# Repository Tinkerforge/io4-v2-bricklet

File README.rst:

IO-4 Bricklet 2.0
=================

This repository contains the firmware source code and the hardware design
files. The documentation generator configs can be found at
https://github.com/Tinkerforge/generators

Repository Content
------------------

software/:
 * examples/: Examples for all supported languages
 * build/: Compiled files
 * src/: Source code of firmware
 * Makefile: Makefile to build project

hardware/:
 * Contains KiCad project files and additionally schematics as PDF

datasheets/:
 * Contains datasheets for sensors and complex ICs that are used

Hardware
--------

The hardware is designed with the open source EDA Suite KiCad
(http://www.kicad.org). Before you are able to open the files,
you have to install the Tinkerforge kicad-libraries
(https://github.com/Tinkerforge/kicad-libraries). You can either clone
them directly in hardware/ or clone them in a separate folder and
symlink them into hardware/
(ln -s kicad_path/kicad-libraries project_path/hardware). After that you
can open the .pro file in hardware/ with KiCad and from there view and
modify the schematics and the PCB layout.

Software
--------

If you want to do your own Brick/Bricklet firmware development we highly
recommend that you use our build environment setup script and read the
tutorial (https://www.tinkerforge.com/en/doc/Tutorials/Tutorial_Build_Environment/Tutorial.html).

To compile the C code we recommend you to install the newest GNU Arm Embedded
Toolchain (https://launchpad.net/gcc-arm-embedded/+download).
You also need to install bricklib2 (https://github.com/Tinkerforge/bricklib2).

You can either clone it directly in software/src/ or clone it in a
separate folder and symlink it into software/src/
(ln -s bricklib_path/bricklib2 project_path/software/src/). Finally make sure to
have CMake installed (http://www.cmake.org/cmake/resources/software.html).

After that you can build the firmware by invoking make in software/.
The firmware (.zbin) can then be found in software/build/ and uploaded
with brickv (click button "Flashing" on start screen).

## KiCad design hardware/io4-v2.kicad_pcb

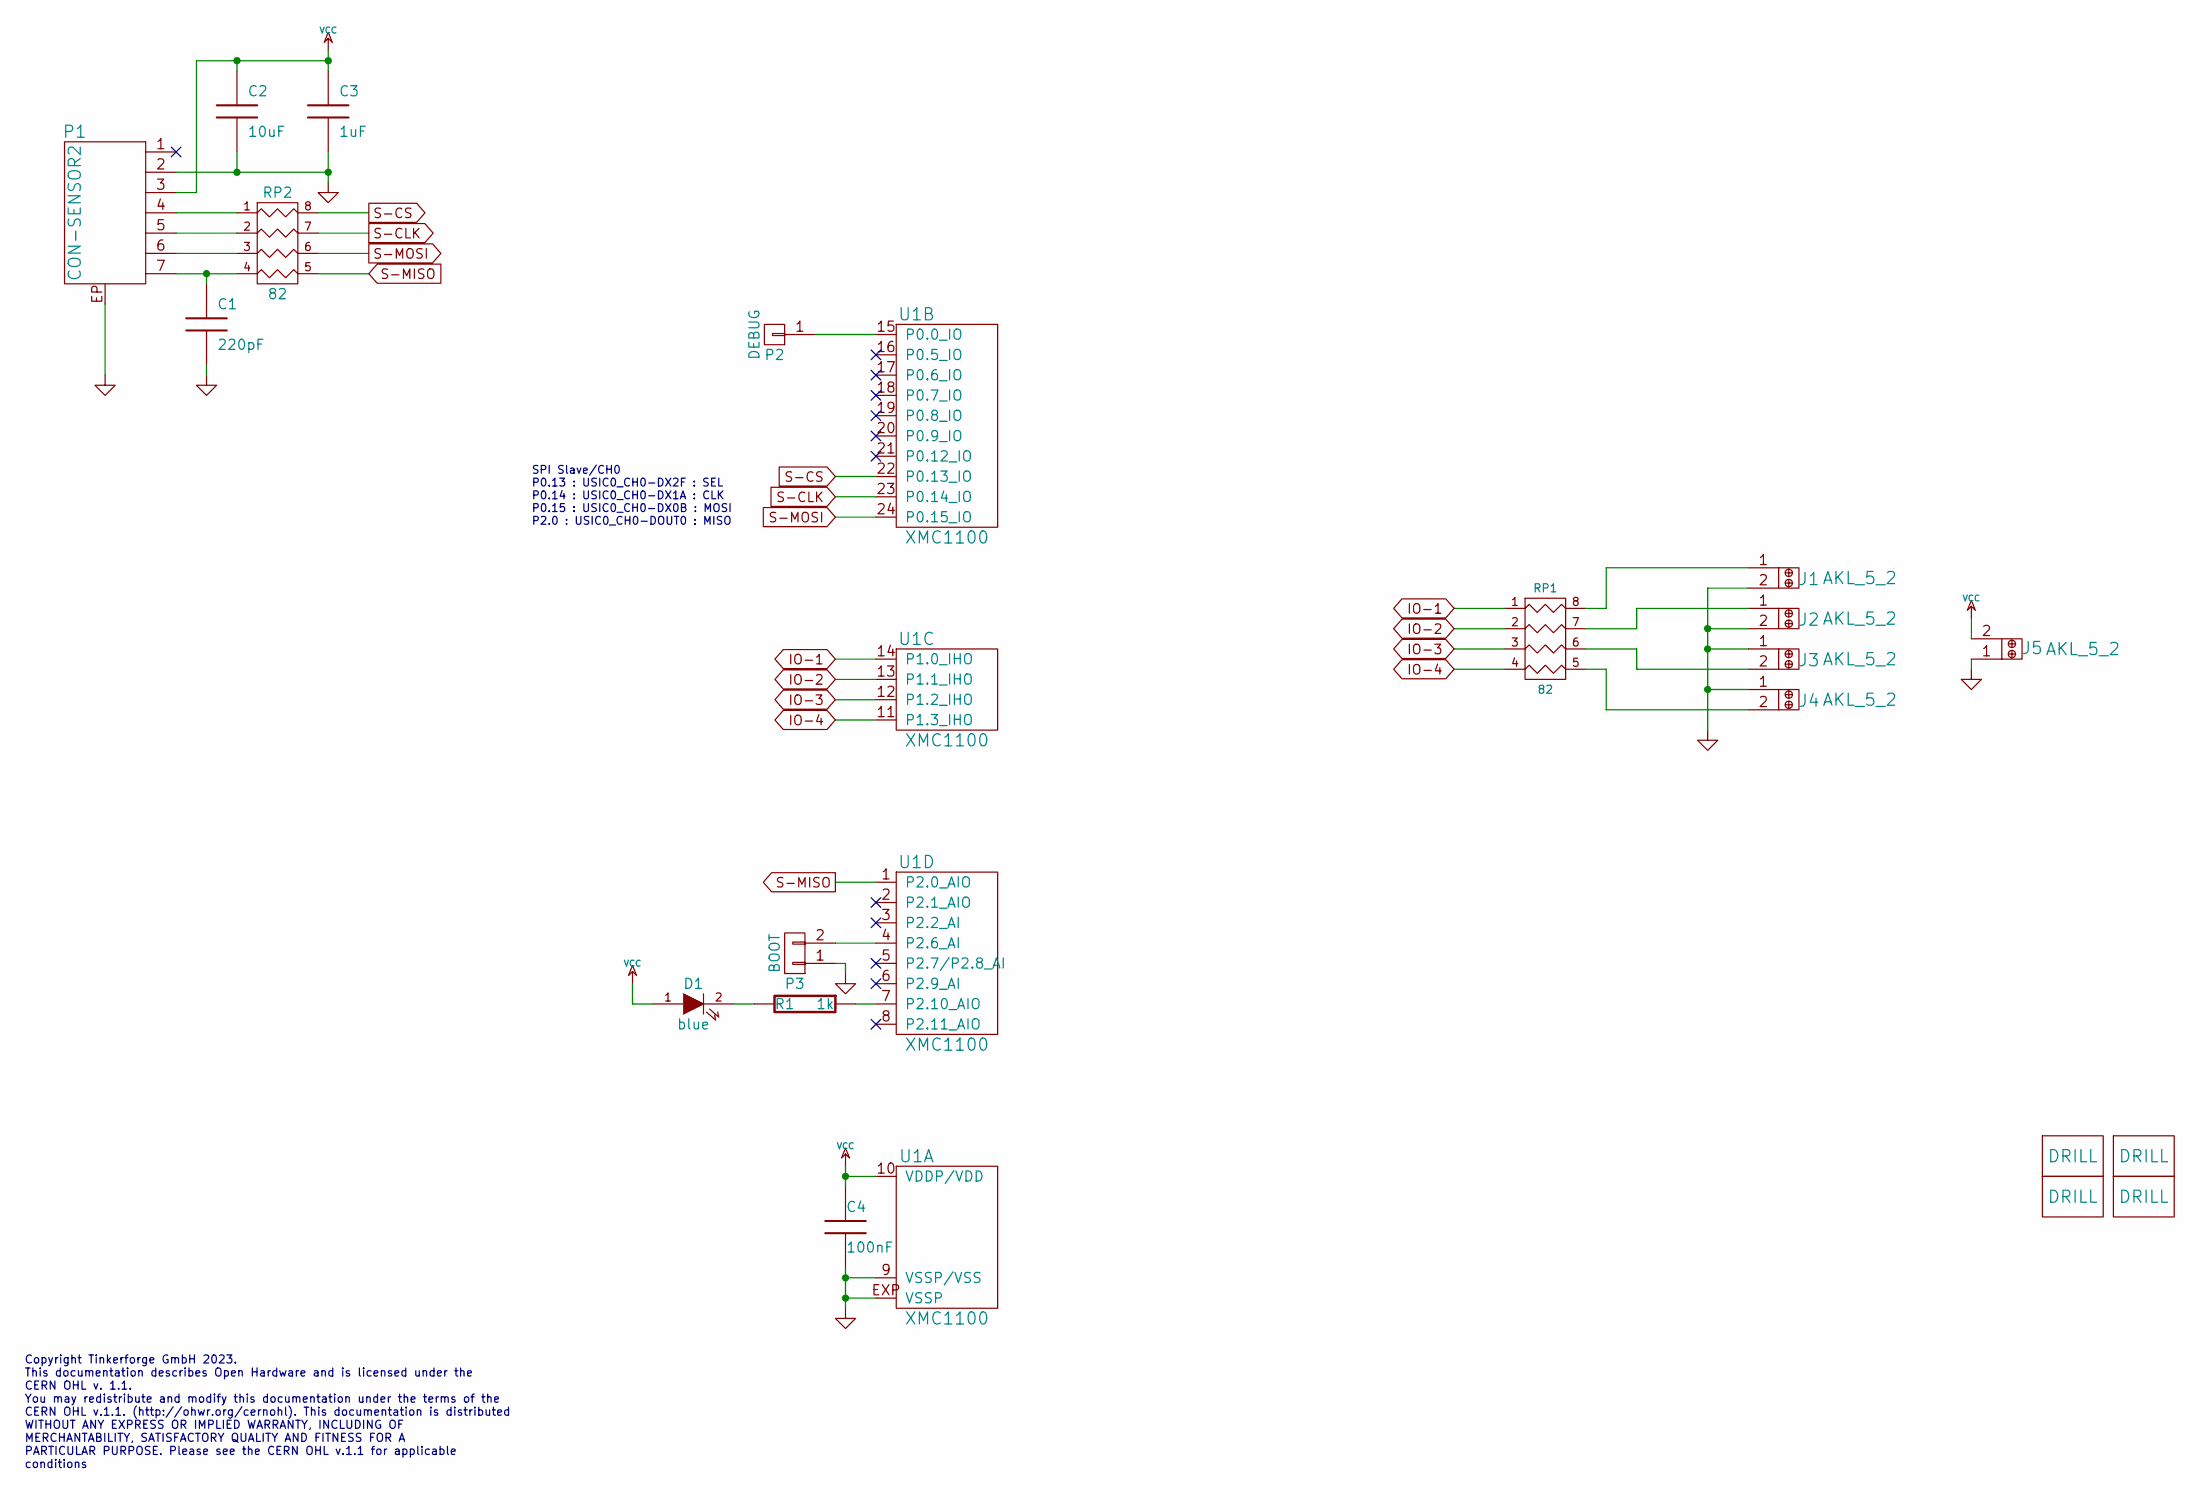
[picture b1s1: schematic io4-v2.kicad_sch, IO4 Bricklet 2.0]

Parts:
C1: 220pF; C0402F
C2: 10uF; C0805
C3: 1uF; C0603F
C4: 100nF; C0603F
D1: blue; D0603F
J1, J2, J3, J4, J5: AKL_5_2
P1: CON-SENSOR2
P2: DEBUG; DEBUG_PAD
P3: BOOT; SolderJumper
R1: 1k; R0603F
RP1, RP2: 82; 4X0402
U1: XMC1100; QFN24-4x4mm-0.5mm
U2, U3, U4, U5: DRILL; DRILL_NP

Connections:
GND: C1.2, C2.2, C3.2, C4.2, J1.2, J2.2, J3.1, J4.1, J5.1, P1.2, P1.EP, P3.1, U1.9 (VSSP/VSS), U1.EXP (VSSP)
IO-1: RP1.1, U1.14 (P1.0_IHO)
IO-2: RP1.2, U1.13 (P1.1_IHO)
IO-3: RP1.3, U1.12 (P1.2_IHO)
IO-4: RP1.4, U1.11 (P1.3_IHO)
unnamed: C1.1, P1.7, RP2.4
unnamed: D1.2 (K), R1.2
unnamed: J1.1, RP1.8 (R1)
unnamed: J2.1, RP1.7 (R2)
unnamed: J3.2, RP1.6 (R3)
unnamed: J4.2, RP1.5 (R4)
unnamed: P1.4, RP2.1
unnamed: P1.5, RP2.2
unnamed: P1.6, RP2.3
unnamed: P2.1, U1.15 (P0.0_IO)
unnamed: P3.2, U1.4 (P2.6_AI)
unnamed: R1.1, U1.7 (P2.10_AIO)
S-CLK: RP2.7 (R2), U1.23 (P0.14_IO)
S-CS: RP2.8 (R1), U1.22 (P0.13_IO)
S-MISO: RP2.5 (R4), U1.1 (P2.0_AIO)
S-MOSI: RP2.6 (R3), U1.24 (P0.15_IO)
VCC: C2.1, C3.1, C4.1, D1.1 (A), J5.2, P1.3, U1.10 (VDDP/VDD)

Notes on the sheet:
Copyright Tinkerforge GmbH 2023. This documentation describes Open Hardware and is licensed under the CERN OHL v. 1.1. You may redistribute and modify this documentation under the terms of the CERN OHL v.1.1. (http://ohwr.org/cernohl). This documentation is distributed WITHOUT ANY EXPRESS OR IMPLIE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
SPI Slave/CH0 P0.13 : USIC0_CH0-DX2F : SEL P0.14 : USIC0_CH0-DX1A : CLK P0.15 : USIC0_CH0-DX0B : MOSI P2.0 : USIC0_CH0-DOUT0 : MISO

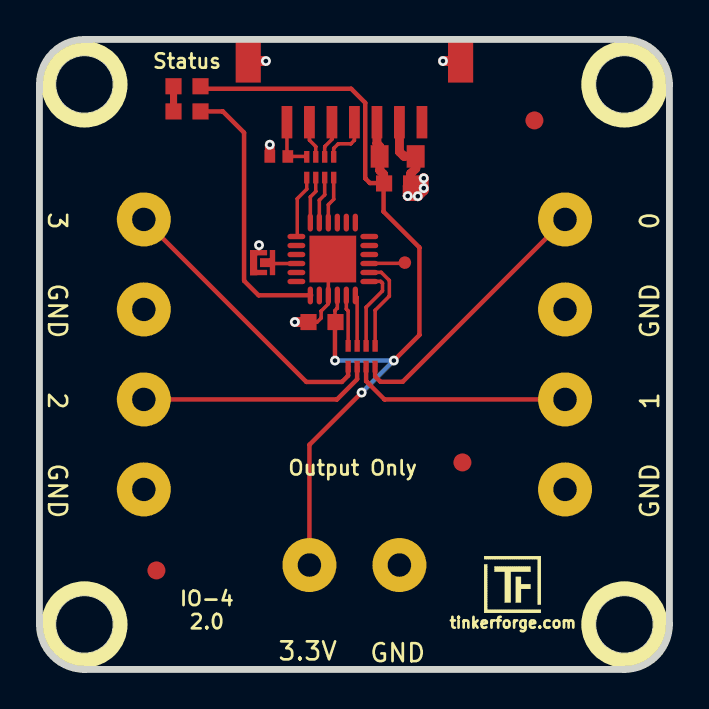
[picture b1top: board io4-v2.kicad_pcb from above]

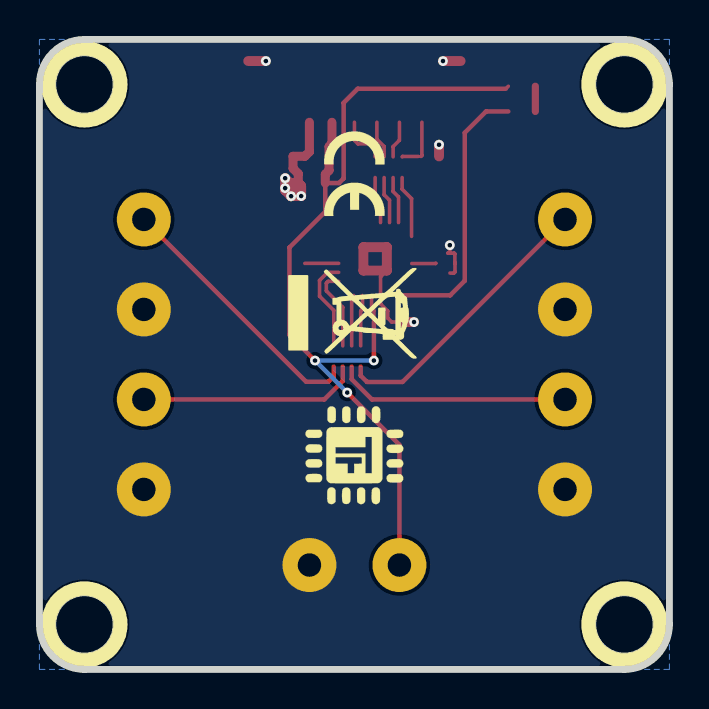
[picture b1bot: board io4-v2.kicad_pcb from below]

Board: 2 copper layers, 35.0 x 35.0 mm, 27 parts (2 on the bottom side), 22 nets.

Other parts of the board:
Fiducial_Mark: VAL**; Fiducial_Mark
Fiducial_Mark#2, Fiducial_Mark#3: VAL**; Fiducial_Mark
Ref**: Val**; Logo_31x31
VAL: WEEE_7mm
VAL#2: CE_5mm

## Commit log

2018-01-16 Add readme and license
2018-01-16 Add initial schemativ
2018-01-17 Add footprint of U1
2018-01-17 Add PCB
2018-02-12 fix status text
2018-02-20 Add .gitignore
2018-02-20 Cleanup KiCad libraries config
    Ensure LibDir=kicad-libraries and LibName1=tinkerforge.
    Remove special library.
2018-02-22 Specify R1
2018-02-22 Change value of Rp from 100 to 82 ohms
2018-02-22 Specify Status-LED color
2018-03-15 fix status text orientation
2018-03-16 change description text
2018-03-27 specify processor
2018-03-27 specify led color
2018-03-27 specify resistor
2018-04-03 Firmware implemented and compiles but is under test
2018-04-04 Fix input value changed callback implementation
2018-04-04 Disable logging
2018-04-04 Use tabs
2018-04-04 Get rid of ternary operators (No hope in Obfuscated C Code Contest!)
2018-04-05 Add tests
2018-04-05 Edge counter fix:
    1. Initially configure edge counter with 100ms debounce period as the
    initial configuration of the channels are input pull-up.
    2. When a channel is being configured from output to input then reset and
    start edge counter. Disable the edge counter if the channel is being
    configured as an output
2018-04-05 Fix typos
2018-04-09 Fix monoflop remaining time calculation
2018-04-23 Add 3d model (*.FCStd & *.step)
2018-05-04 Rename files
2018-05-04 Add schematic PDF
2018-05-29 Remove unnecessary get-selected-value function
2018-06-05 Add support for PWM API
2018-06-07 Update changelog for initial release
2018-06-18 Change capacitor footprint(s) to C0402F
2018-06-28 Fix readme
2018-07-11 Add Makefile with docker support
2018-07-11 Remove obsolete generate_makefile scripts
2018-07-11 Update directory structure and build instructions
2018-10-04 Increase version for new release (changes in bricklib2)
2018-10-04 Add rev to changelog
2018-11-12 Add examples for IO4 Bricklet 2.0
2018-12-14 Add go examples.
2018-12-18 go: Change import path.
2018-12-18 go: Change import path again.
2018-12-20 rust: Fix result variable names in examples.
2019-01-24 mqtt: Add examples.
2019-01-24 mqtt: Fix example header.
2019-01-24 mqtt: Remove executable bit in example permissions.
2019-01-24 go: Minor example fixes.
2019-01-24 mqtt: Minor example fixes.
2019-01-29 rust: Fix unused loop index.
2019-02-25 Firmware fix:
    1. Init GPIO only once and later use GPIO Mode to configure the pins.
    2. Reconfigure only when required
2019-02-27 Add changelog for 2.0.2, increase version
2019-02-27 Add rev for 2.0.2
2019-03-28 mqtt: Fix whitespace.
2019-05-07 Abort active monoflop/PWM on set-configuration call for output
    Don't clear monoflop time on monoflop done/abort to match documentation
2019-08-22 c: Adapt to bindings changes
2020-01-13 examples: Use python3 input instead of python2 raw_input.
2020-01-13 examples: mqtt: Remove trailing whitespace.
2020-03-16 Whitespace
2020-04-07 examples: rust: Always block when calling bindings functions.
2020-08-19 Add uc examples.
2020-08-25 uc: Fix whitespace
2020-08-26 mqtt: Update for loop style
2020-08-27 uc: Fix warnings.
2020-08-31 uc: Use fixed-with placeholders in format strings.
2020-09-02 uc: Add example driver note.
2021-05-06 Add input examples
2021-05-06 mathematica: Fix broken syntax
2021-09-29 Add LabVIEW examples
2021-10-25 Update KiCad link
    https://www.kicad.org/blog/2021/10/Avoid-links-to-former-kicad-domain/
2022-04-19 examples: uc: Rename TF_HalContext to TF_HAL.
2022-04-27 uc: Adapt to bindings changes
2022-05-10 go: Fix format string
2022-07-06 Add license files.
2023-01-27 fix schematic
2023-01-27 Data Cleanup
2025-05-14 Fix boot pad config
2025-05-14 Add CaptureInput callback
2025-05-15 Add CaptureInput callback example
2025-05-15 Fix typo
2025-05-15 Add 2.0.5 notes to changelog

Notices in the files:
hardware/io4-v2.kicad_pcb:
Licensed under CERN OHL v.1.1
Copyright (©) 2023, T.Schneidermann
